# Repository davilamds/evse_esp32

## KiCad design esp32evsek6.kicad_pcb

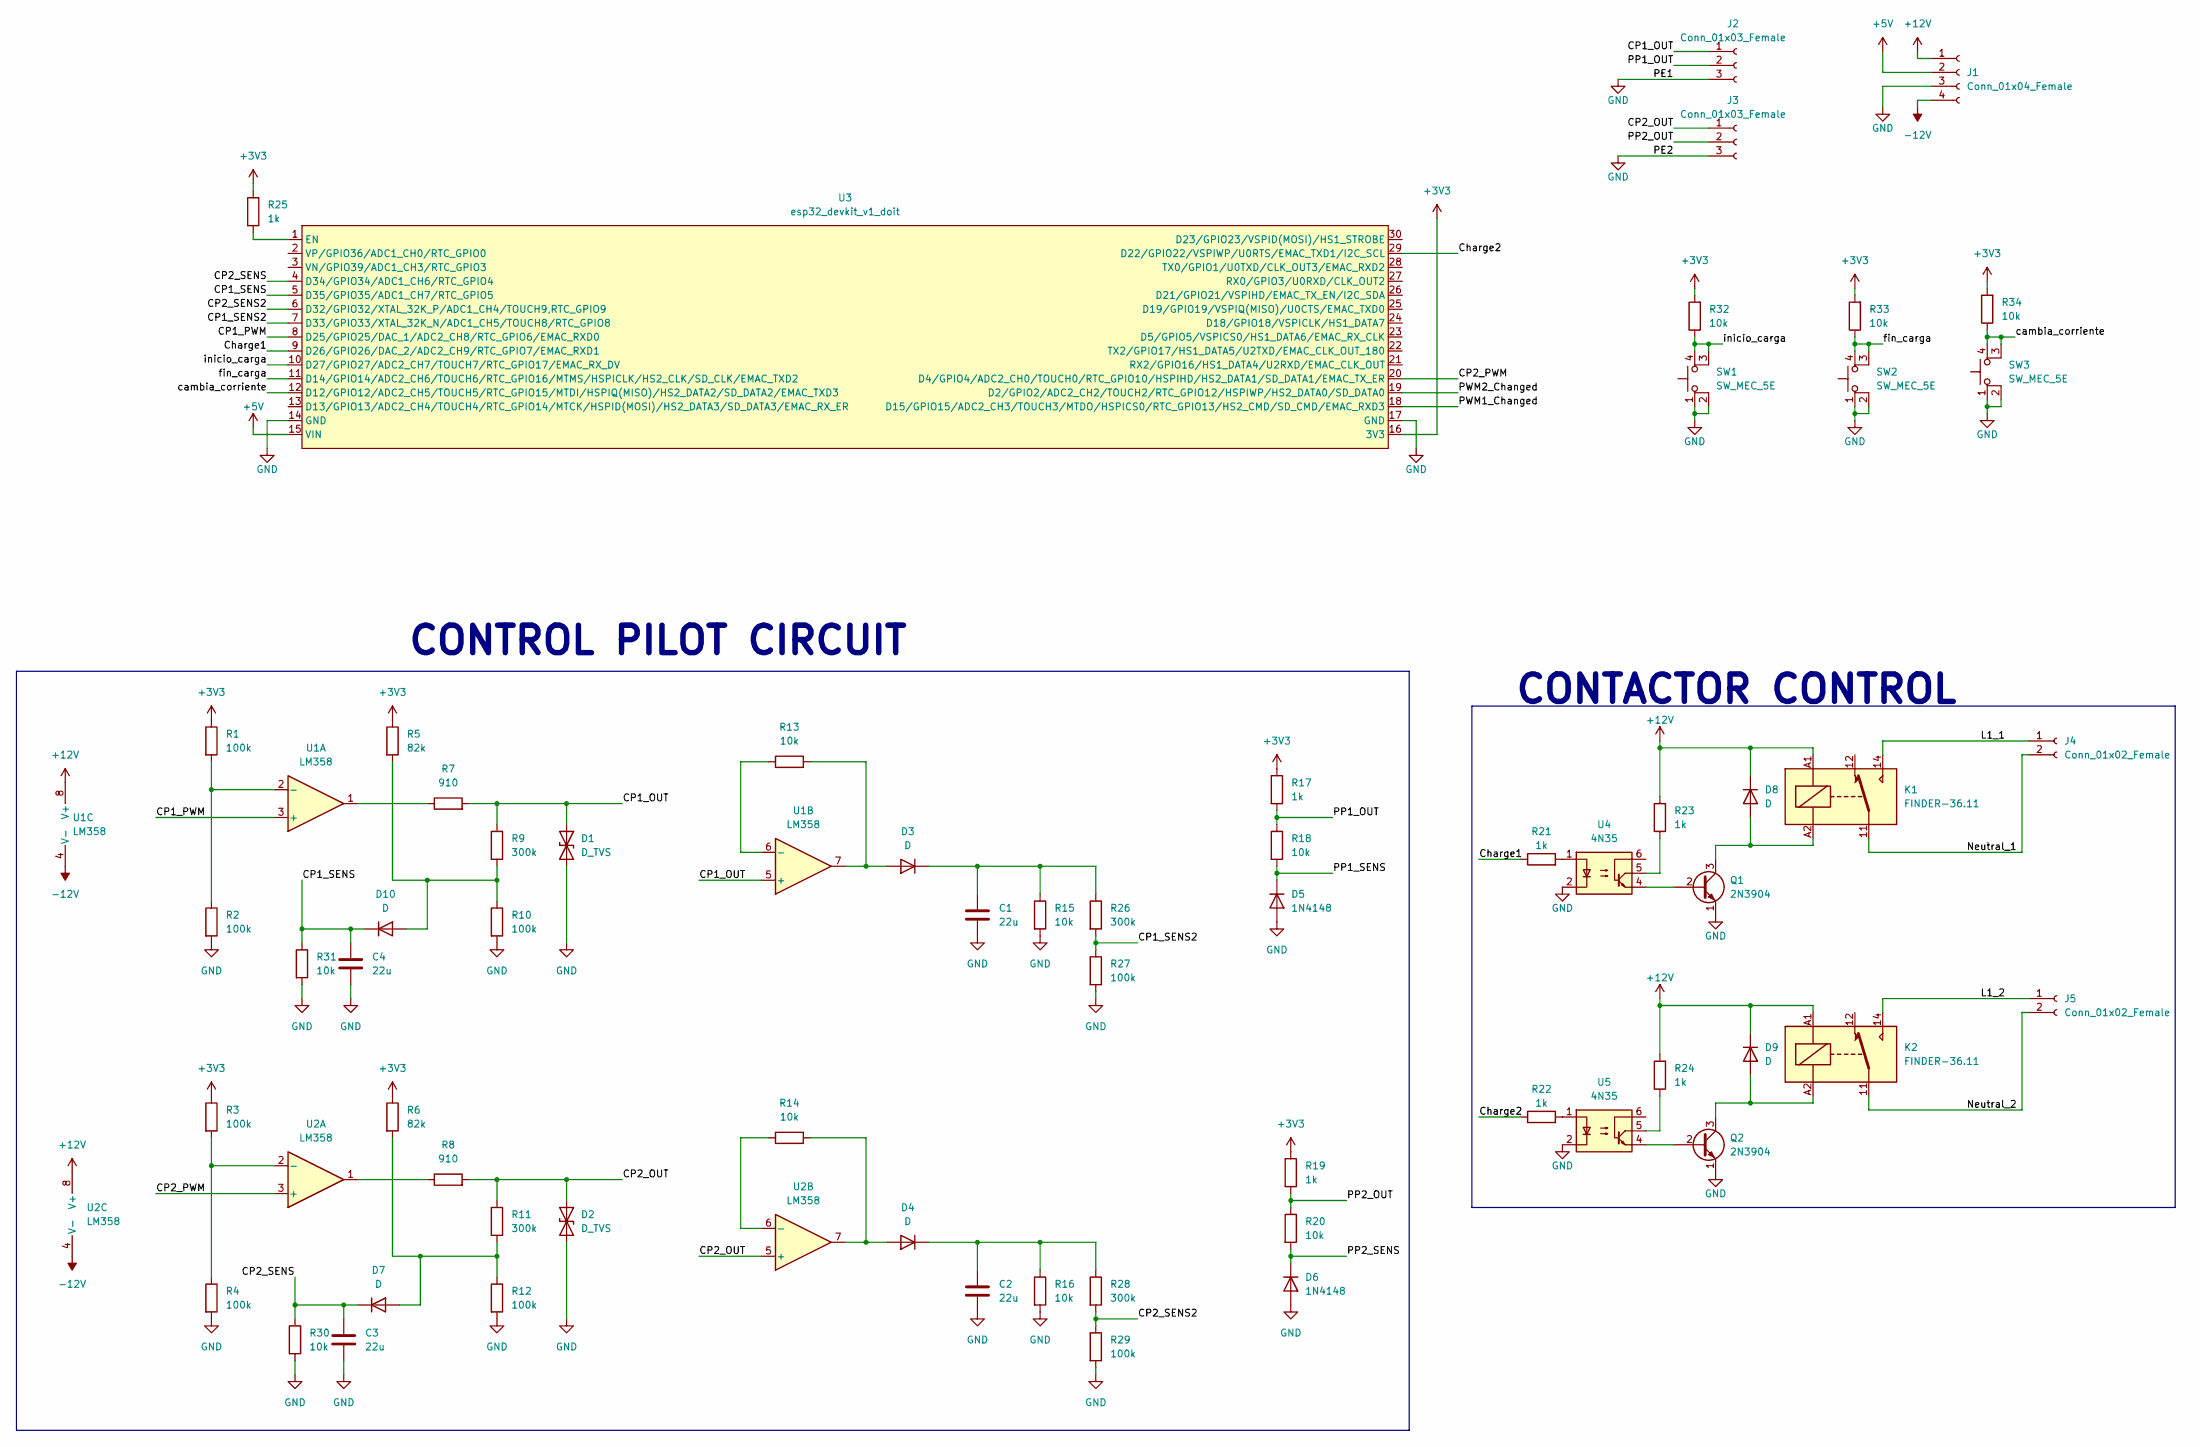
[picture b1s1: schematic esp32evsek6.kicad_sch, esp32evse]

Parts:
C1, C2, C3, C4: 22u; C_Radial_D5.0mm_H7.0mm_P2.00mm
D1, D2: D_TVS; D_DO-35_SOD27_P7.62mm_Horizontal
D3, D4, D7, D10: D; D_T-1_P10.16mm_Horizontal
D5, D6: 1N4148; D_DO-35_SOD27_P7.62mm_Horizontal
D8, D9: D; D_DO-35_SOD27_P7.62mm_Horizontal
J1: Conn_01x04_Female; JST_NV_B04P-NV_1x04_P5.00mm_Vertical
J2, J3: Conn_01x03_Female; JST_NV_B03P-NV_1x03_P5.00mm_Vertical
J4, J5: Conn_01x02_Female; JST_NV_B02P-NV_1x02_P5.00mm_Vertical
K1, K2: FINDER-36.11; Relay_SPDT_Finder_36.11
Q1, Q2: 2N3904; TO-92_Inline_Wide
R1, R2, R3, R4, R10, R12, R27, R29: 100k; R_Axial_DIN0204_L3.6mm_D1.6mm_P7.62mm_Horizontal
R5, R6: 82k; R_Axial_DIN0204_L3.6mm_D1.6mm_P7.62mm_Horizontal
R7, R8: 910; R_Axial_DIN0204_L3.6mm_D1.6mm_P7.62mm_Horizontal
R9, R11, R26, R28: 300k; R_Axial_DIN0204_L3.6mm_D1.6mm_P7.62mm_Horizontal
R13, R14, R15, R16, R18, R20, R30, R31, R32, R33, R34: 10k; R_Axial_DIN0204_L3.6mm_D1.6mm_P7.62mm_Horizontal
R17, R19, R21, R22, R23, R24, R25: 1k; R_Axial_DIN0204_L3.6mm_D1.6mm_P7.62mm_Horizontal
SW1, SW2, SW3: SW_MEC_5E; SW_TH_Tactile_Omron_B3F-10xx
U1, U2: LM358; DIP-8_W7.62mm_Socket_LongPads
U3: esp32_devkit_v1_doit; ESP32_Devkit_v1_doit_30pin
U4, U5: 4N35; DIP-6_W7.62mm_Socket_LongPads

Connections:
+3V3: R1.1, R3.1, R5.1, R6.1, R17.1, R19.1, R25.1, R32.2, R33.2, R34.2, U3.16 (3V3)
+5V: J1.2, U3.15 (VIN)
+12V: D8.1 (K), D9.1 (K), J1.1, K1.A1, K2.A1, R23.2, R24.2, U1.8 (V+), U2.8 (V+)
-12V: J1.4, U1.4 (V-), U2.4 (V-)
/CP1_OUT: D1.1 (A1), J2.1, R7.2, R9.1, U1.5 (+)
/CP1_PWM: U1.3 (+), U3.8 (D25/GPIO25/DAC_1/ADC2_CH8/RTC_GPIO6/EMA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)
/CP1_SENS: C4.1, D10.1 (K), R31.1, U3.5 (D35/GPIO35/ADC1_CH7/RTC_GPIO5)
/CP1_SENS2: R26.2, R27.1, U3.7 (D33/GPIO33/XTAL_32K_N/ADC1_CH5/TOUCH8/R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)
/CP2_OUT: D2.1 (A1), J3.1, R8.2, R11.1, U2.5 (+)
/CP2_PWM: U2.3 (+), U3.20 (D4/GPIO4/ADC2_CH0/TOUCH0/RTC_GPIO10/HSP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)
/CP2_SENS: C3.1, D7.1 (K), R30.1, U3.4 (D34/GPIO34/ADC1_CH6/RTC_GPIO4)
/CP2_SENS2: R28.2, R29.1, U3.6 (D32/GPIO32/XTAL_32K_P/ADC1_CH4/TOUCH9,R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)
/Charge1: R21.1, U3.9 (D26/GPIO26/DAC_2/ADC2_CH9/RTC_GPIO7/EMA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)
/Charge2: R22.1, U3.29 (D22/GPIO22/VSPIWP/U0RTS/EMAC_TXD1/I2C_S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)
/L1_1: J4.1, K1.14
/L1_2: J5.1, K2.14
/Neutral_1: J4.2, K1.11
/Neutral_2: J5.2, K2.11
/PP1_OUT: J2.2, R17.2, R18.1
/PP1_SENS: D5.1 (K), R18.2
/PP2_OUT: J3.2, R19.2, R20.1
/PP2_SENS: D6.1 (K), R20.2
/PWM1_Changed: U3.18 (D15/GPIO15/ADC2_CH3/TOUCH3/MTDO/HSPICS0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)
/PWM2_Changed: U3.19 (D2/GPIO2/ADC2_CH2/TOUCH2/RTC_GPIO12/HSP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)
/cambia_corriente: R34.1, SW3.3 (K), SW3.4 (A), U3.12 (D12/GPIO12/ADC2_CH5/TOUCH5/RTC_GPIO15/M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)
/fin_carga: R33.1, SW2.3 (K), SW2.4 (A), U3.11 (D14/GPIO14/ADC2_CH6/TOUCH6/RTC_GPIO16/M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)
/inicio_carga: R32.1, SW1.3 (K), SW1.4 (A), U3.10 (D27/GPIO27/ADC2_CH7/TOUCH7/RTC_GPIO17/E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)
GND: C1.2, C2.2, C3.2, C4.2, D1.2 (A2), D2.2 (A2), D5.2 (A), D6.2 (A), J1.3, J2.3, J3.3, Q1.1 (E), Q2.1 (E), R2.2, R4.2, R10.2, R12.2, R15.2, R16.2, R27.2, R29.2, R30.2, R31.2, SW1.1, SW1.2, SW2.1, SW2.2, SW3.1, SW3.2, U3.14 (GND), U3.17 (GND), U4.2, U5.2
unnamed: C1.1, D3.1 (K), R15.1, R26.1
unnamed: C2.1, D4.1 (K), R16.1, R28.1
unnamed: D3.2 (A), R13.2, U1.7
unnamed: D4.2 (A), R14.2, U2.7
unnamed: D7.2 (A), R6.2, R11.2, R12.1
unnamed: D8.2 (A), K1.A2, Q1.3 (C)
unnamed: D9.2 (A), K2.A2, Q2.3 (C)
unnamed: D10.2 (A), R5.2, R9.2, R10.1
unnamed: Q1.2 (B), U4.4
unnamed: Q2.2 (B), U5.4
unnamed: R1.2, R2.1, U1.2 (-)
unnamed: R3.2, R4.1, U2.2 (-)
unnamed: R7.1, U1.1
unnamed: R8.1, U2.1
unnamed: R13.1, U1.6 (-)
unnamed: R14.1, U2.6 (-)
unnamed: R21.2, U4.1
unnamed: R22.2, U5.1
unnamed: R23.1, U4.5
unnamed: R24.1, U5.5
unnamed: R25.2, U3.1 (EN)

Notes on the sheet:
CONTACTOR CONTROL
CONTROL PILOT CIRCUIT

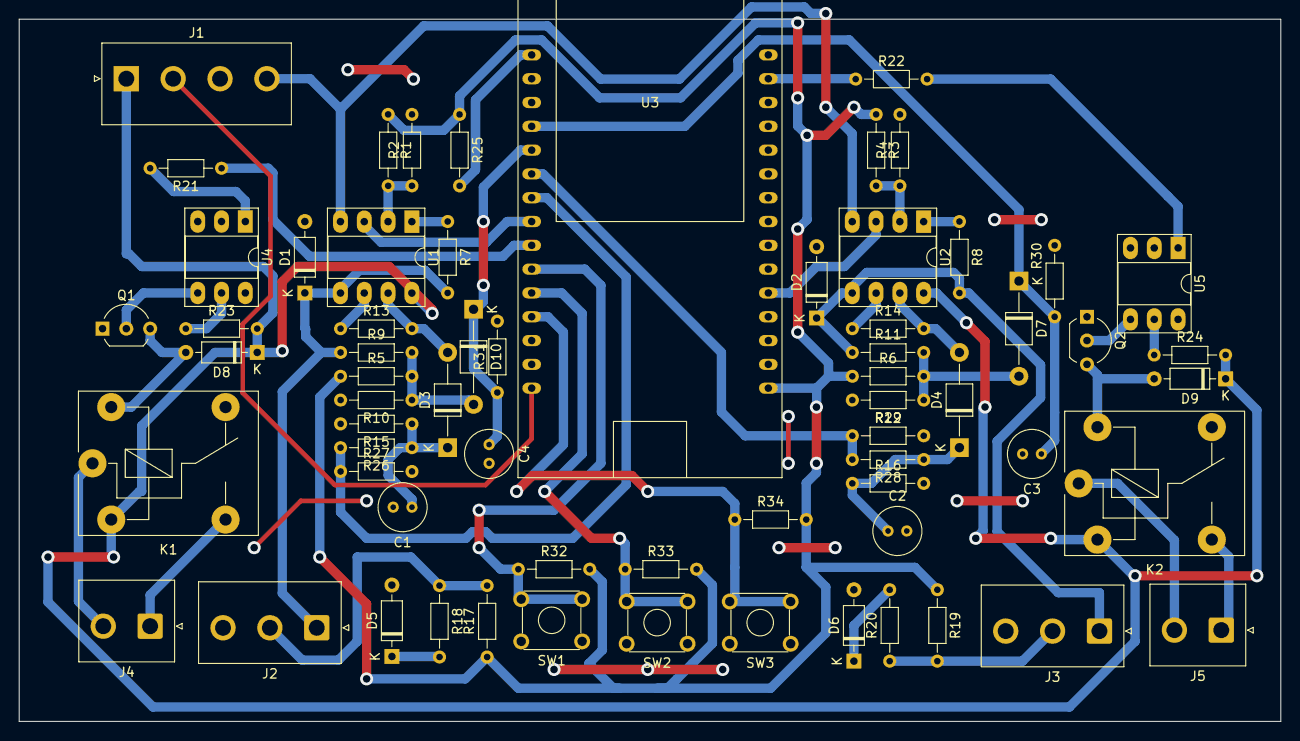
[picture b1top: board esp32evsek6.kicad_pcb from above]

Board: 2 copper layers, 134.6 x 74.9 mm, 65 parts (0 on the bottom side), 47 nets.
